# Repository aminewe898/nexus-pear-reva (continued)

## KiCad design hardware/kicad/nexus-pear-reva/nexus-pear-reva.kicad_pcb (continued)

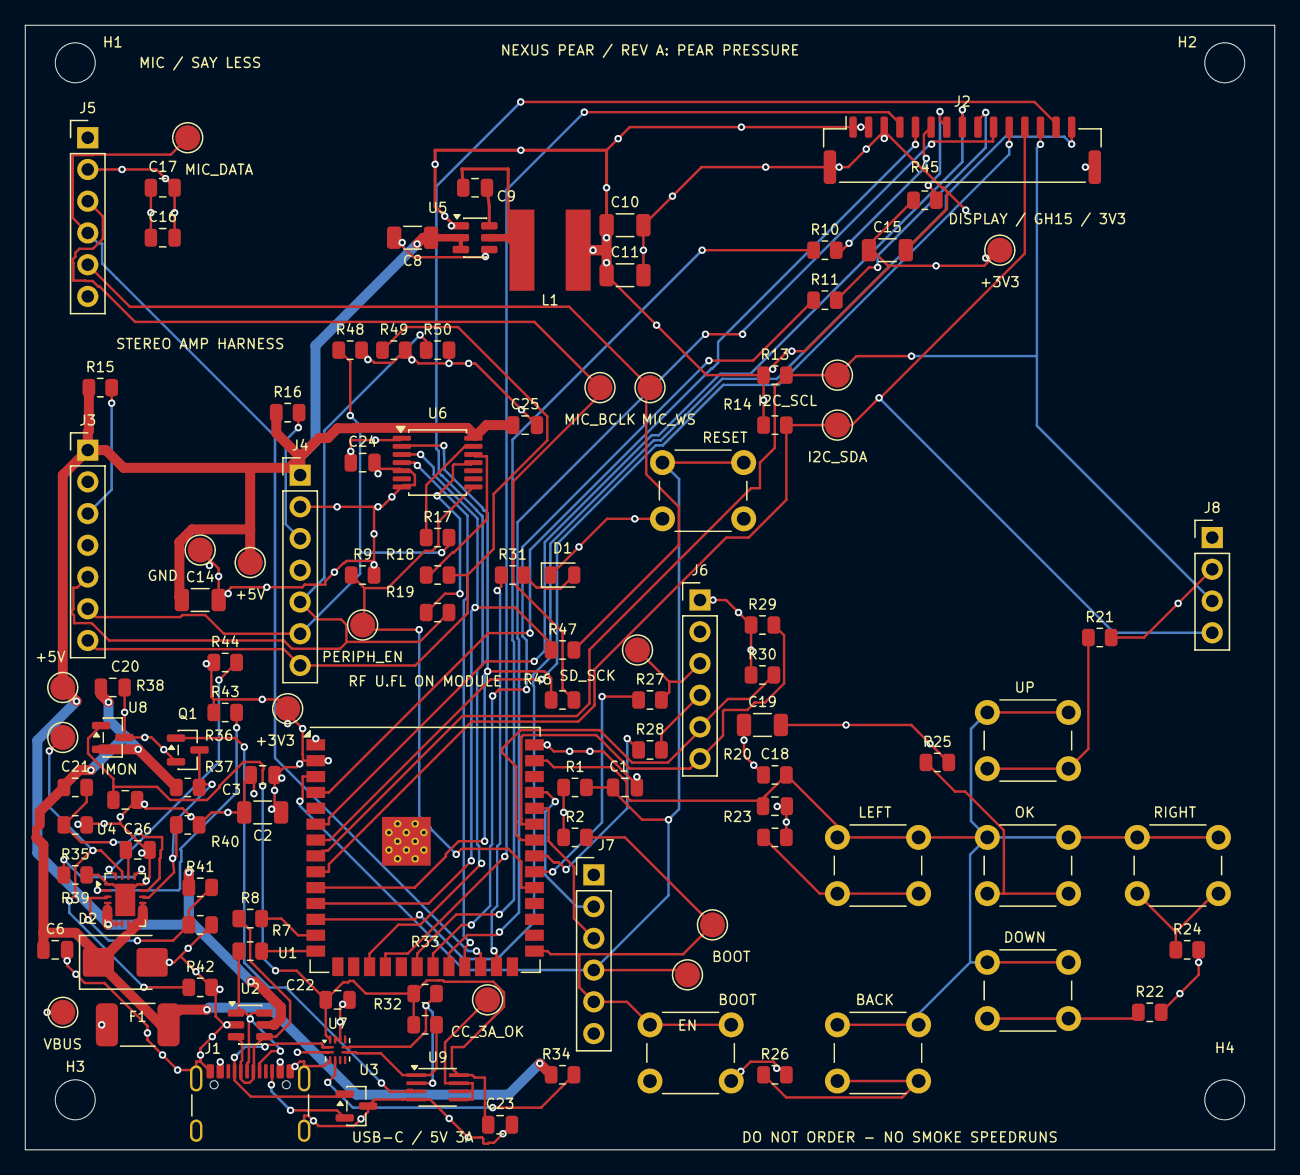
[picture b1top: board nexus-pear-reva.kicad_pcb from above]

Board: 4 copper layers, 100.0 x 90.0 mm, 117 parts (0 on the bottom side), 75 nets.

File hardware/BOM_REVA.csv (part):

"Reference","Qty","Value","Description","Manufacturer","MPN","Package","Supplier","Supplier SKU","Unit Cost","Extended Cost","Availability","Datasheet URL","Notes","Currency"
"U1","1","ESP32-S3-WROOM-1U-N16R8","Manufacturer pin table checked; GPIO35/36/37 reserved for octal PSRAM. External RF socket.","Espressif","ESP32-S3-WROOM-1U-N16R8","ESP32-S3-WROOM-1U","RFQ required","",,"","Exact live price and stock unconfirmed","https://www.espressif.com/sites/default/files/documentation/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","CANDIDATE; DO NOT ORDER. Manufacturer pin table checked; GPIO35/36/37 reserved for octal PSRAM. External RF socket.",""
"R1","1","10k","1% 0805 thick-film; exact value and pin mapping explicit","Yageo","RC0805FR-0710KL","R_0805_2012Metric","RFQ required","",,"","Exact live price and stock unconfirmed","https://www.yageo.com/en/ProductSearch","CANDIDATE; DO NOT ORDER. 1% 0805 thick-film; exact value and pin mapping explicit",""
"C1","1","1u","Ceramic; exact DC-bias and sourcing review pending; do not substitute voltage rating blindly","Murata","GRM21BR71A105KA01L","C_0805_2012Metric","RFQ required","",,"","Exact live price and stock unconfirmed","https://www.murata.com/en-global/products/capacitor/mlcc","CANDIDATE; DO NOT ORDER. Ceramic; exact DC-bias and sourcing review pending; do not substitute voltage rating blindly",""
"C2","1","22u","Ceramic; exact DC-bias and sourcing review pending; do not substitute voltage rating blindly","Murata","GRM31CR61A226KE19L","C_1206_3216Metric","RFQ required","",,"","Exact live price and stock unconfirmed","https://www.murata.com/en-global/products/capacitor/mlcc","CANDIDATE; DO NOT ORDER. Ceramic; exact DC-bias and sourcing review pending; do not substitute voltage rating blindly",""
"C3","1","100n","Ceramic; exact DC-bias and sourcing review pending; do not substitute voltage rating blindly","Murata","GRM21BR71H104KA01L","C_0805_2012Metric","RFQ required","",,"","Exact live price and stock unconfirmed","https://www.murata.com/en-global/products/capacitor/mlcc","CANDIDATE; DO NOT ORDER. Ceramic; exact DC-bias and sourcing review pending; do not substitute voltage rating blindly",""
"R2","1","10k","1% 0805 thick-film; exact value and pin mapping explicit","Yageo","RC0805FR-0710KL","R_0805_2012Metric","RFQ required","",,"","Exact live price and stock unconfirmed","https://www.yageo.com/en/ProductSearch","CANDIDATE; DO NOT ORDER. 1% 0805 thick-film; exact value and pin mapping explicit",""
"J1","1","USB-C 5V / USB2 FS","Fixed sink; no PD, no host; shield bonded to ground. Exact footprint requires final dimension audit.","GCT","USB4105-GF-A","USB_C_Receptacle_GCT_USB4105-xx-A_16P_TopMnt_Horizontal","RFQ required","",,"","Exact live price and stock unconfirmed","https://gct.co/files/drawings/usb4105.pdf","CANDIDATE; DO NOT ORDER. Fixed sink; no PD, no host; shield bonded to ground. Exact footprint requires final dimension audit.",""
"R7","1","22","1% 0805 thick-film; exact value and pin mapping explicit","Yageo","RC0805FR-0722RL","R_0805_2012Metric","RFQ required","",,"","Exact live price and stock unconfirmed","https://www.yageo.com/en/ProductSearch","CANDIDATE; DO NOT ORDER. 1% 0805 thick-film; exact value and pin mapping explicit",""
"R8","1","22","1% 0805 thick-film; exact value and pin mapping explicit","Yageo","RC0805FR-0722RL","R_0805_2012Metric","RFQ required","",,"","Exact live price and stock unconfirmed","https://www.yageo.com/en/ProductSearch","CANDIDATE; DO NOT ORDER. 1% 0805 thick-film; exact value and pin mapping explicit",""
"U2","1","USBLC6-2SC6","USB data ESD; bias from protected main 5V, not raw VBUS","STMicroelectronics","USBLC6-2SC6","SOT-23-6","RFQ required","",,"","Exact live price and stock unconfirmed","https://www.st.com/resource/en/datasheet/usblc6-2.pdf","CANDIDATE; DO NOT ORDER. USB data ESD; bias from protected main 5V, not raw VBUS",""
"U3","1","PESD5V0S2BT CC ESD","Ground-referenced CC ESD; no rail injection. Not a 20V CC-to-VBUS short protector.","Nexperia","PESD5V0S2BT,215","SOT-23","RFQ required","",,"","Exact live price and stock unconfirmed","https://assets.nexperia.com/documents/data-sheet/PESD5V0S2BT.pdf","CANDIDATE; DO NOT ORDER. Ground-referenced CC ESD; no rail injection. Not a 20V CC-to-VBUS short protector.",""
"F1","1","3A / 24V PTC","Manufacturer Low Rho table: 3A hold, 24V, R1max30mOhm; recommended pads 1.78x3.45mm, 3.15mm inner gap. Derates to 2.45A at40C and1.85A at60C.","Littelfuse","1812L300/24SLER","Fuse_1812_4532Metric","DigiKey","18-1812L300/24SLERCT-ND","2.63","2.63","Price/stock captured 2026-10-07","https://www.littelfuse.com/assetdocs/low-rho-datasheet-updat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","CANDIDATE; DO NOT ORDER. Manufacturer Low Rho table: 3A hold, 24V, R1max30mOhm; recommended pads 1.78x3.45mm, 3.15mm inner gap. Derates to 2.45A at40C and1.85A at60C.","USD"
"C6","1","100n","50V X7R raw input decoupling; upstream capacitance below 1uF","Murata","GRM21BR71H104KA01L","C_0805_2012Metric","RFQ required","",,"","Exact live price and stock unconfirmed","https://www.murata.com/en-global/products/capacitor/mlcc","CANDIDATE; DO NOT ORDER. 50V X7R raw input decoupling; upstream capacitance below 1uF",""
"U4","1","TPS25940LRVCR eFuse","Latched eFuse: reverse blocking, UVLO, OVP, ~2.56A limit, controlled rise; only enabled on 3A advertisement","Texas Instruments","TPS25940LRVCR","Texas_RVC0020A_WQFN-20-1EP_3x4mm_P0.5mm_EP1.6x2.6mm","RFQ required","",,"","Exact live price and stock unconfirmed","https://www.ti.com/lit/ds/symlink/tps25940.pdf","CANDIDATE; DO NOT ORDER. Latched eFuse: reverse blocking, UVLO, OVP, ~2.56A limit, controlled rise; only enabled on 3A advertisement",""
"C8","1","10u","Ceramic; exact DC-bias and sourcing review pending; do not substitute voltage rating blindly","Murata","GRM31CR61A106KA01L","C_1206_3216Metric","RFQ required","",,"","Exact live price and stock unconfirmed","https://www.murata.com/en-global/products/capacitor/mlcc","CANDIDATE; DO NOT ORDER. Ceramic; exact DC-bias and sourcing review pending; do not substitute voltage rating blindly",""
"U5","1","AP63203WU-7 3V3 buck","2A fixed 3.3V. Sourcing contradictory; not release-qualified.","Diodes Incorporated","AP63203WU-7","TSOT-23-6","RFQ required","",,"","Exact live price and stock unconfirmed","https://www.diodes.com/assets/Datasheets/AP63200-AP63201-AP6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","CANDIDATE; DO NOT ORDER. 2A fixed 3.3V. Sourcing contradictory; not release-qualified.",""
"C9","1","100n","Ceramic; exact DC-bias and sourcing review pending; do not substitute voltage rating blindly","Murata","GRM21BR71H104KA01L","C_0805_2012Metric","RFQ required","",,"","Exact live price and stock unconfirmed","https://www.murata.com/en-global/products/capacitor/mlcc","CANDIDATE; DO NOT ORDER. Ceramic; exact DC-bias and sourcing review pending; do not substitute voltage rating blindly",""
"L1","1","3.9uH","Bourns C-series recommended pads 2.0x6.5mm, center spacing 4.5mm; local native snapshot corrected against manufacturer drawing.","Bourns","SRN6028C-3R9M","L_Bourns-SRN6028","RFQ required","",,"","Exact live price and stock unconfirmed","https://www.bourns.com/data/global/pdfs/SRN6028C.pdf","CANDIDATE; DO NOT ORDER. Bourns C-series recommended pads 2.0x6.5mm, center spacing 4.5mm; local native snapshot corrected against manufacturer drawing.",""
"C10","1","22u","Ceramic; exact DC-bias and sourcing review pending; do not substitute voltage rating blindly","Murata","GRM31CR61A226KE19L","C_1206_3216Metric","RFQ required","",,"","Exact live price and stock unconfirmed","https://www.murata.com/en-global/products/capacitor/mlcc","CANDIDATE; DO NOT ORDER. Ceramic; exact DC-bias and sourcing review pending; do not substitute voltage rating blindly",""
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
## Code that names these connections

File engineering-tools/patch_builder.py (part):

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setpins('J2',[(i+1,n,n) for i,n in enumerate(['+3V3','+3V3','GND','LCD_MISO','LCD_MOSI','LCD_SCLK','DISPLAY_SD_CS','LCD_CS','LCD_DC','LCD_RST','LCD_BL','I2C_SDA','I2C_SCL','TP_INT','TP_RST'])])
setpins('R10',[(1,'1','LCD_SCLK_SRC'),(2,'2','LCD_SCLK')])
for ref in ('J3','J4'):
 for a in by[ref]['pins']:
  a['net']={'I2S_TX':'AMP_TX','I2S_BCLK':'AMP_BCLK','I2S_WS':'AMP_WS'}.get(a['net'],a['net'])
for ref,a,b in [('R17','AMP_BCLK_BUF','AMP_BCLK'),('R18','AMP_WS_BUF','AMP_WS'),('R19','AMP_TX_BUF','AMP_TX')]:setpins(ref,[(1,'1',a),(2,'2',b)])
# Microphone clocks remain 3.3V; amplifier clocks pass through the fail-safe buffer.
for a in by['J5']['pins']:a['net']={'I2S_BCLK':'MIC_BCLK','I2S_WS':'MIC_WS'}.get(a['net'],a['net'])
for ref,net in [('TP7','+3V3'),('TP8','+5V'),('TP11','MIC_BCLK'),('TP12','MIC_WS'),('TP16','CC_3A_OK'),('TP17','IMON')]:setpins(ref,[(1,net,net)]);change(ref,value=net)
change('R21',mpn='RC0805JR-070RL',notes='Zero-ohm jumper; resistor tolerance code J, not F')
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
